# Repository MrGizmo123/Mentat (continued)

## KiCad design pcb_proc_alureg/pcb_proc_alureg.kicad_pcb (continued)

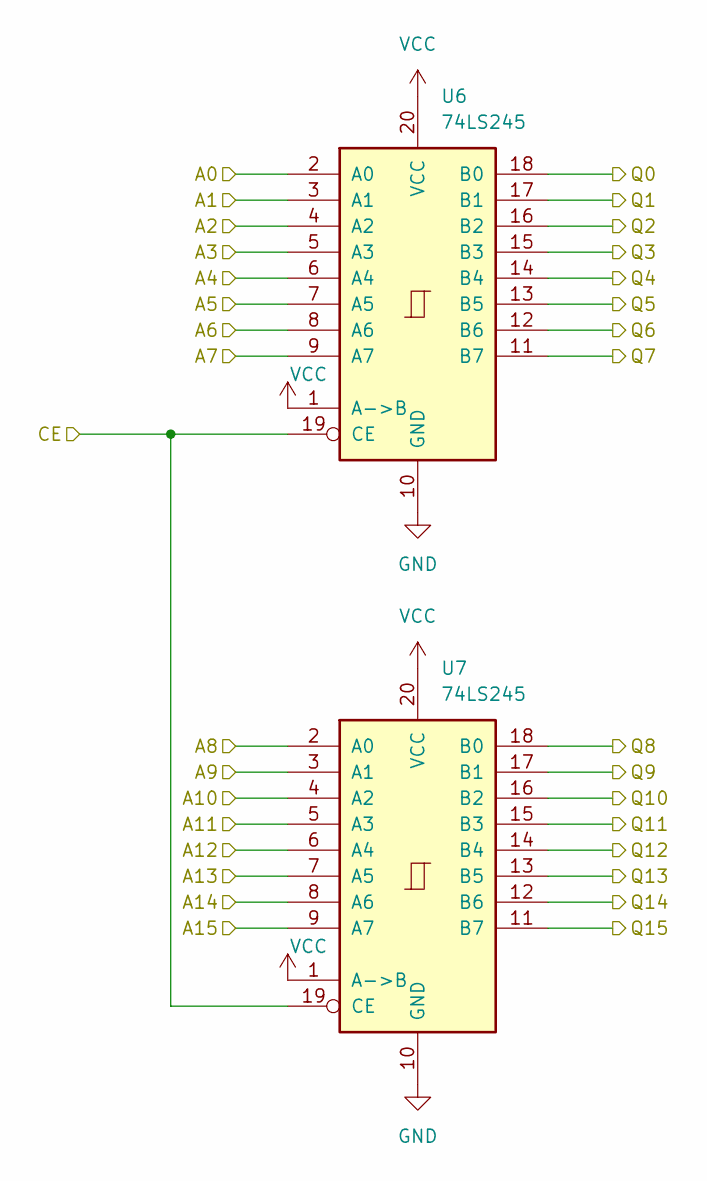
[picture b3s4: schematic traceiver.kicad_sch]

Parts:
U6, U7: 74LS245; DIP-20_W7.62mm_Socket_LongPads

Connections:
/Display/D0: U6.2 (A0); also elsewhere on the board
/Display/D1: U6.3 (A1); also elsewhere on the board
/Display/D2: U6.4 (A2); also elsewhere on the board
/Display/D3: U6.5 (A3); also elsewhere on the board
/Display/D4: U6.6 (A4); also elsewhere on the board
/Display/D5: U6.7 (A5); also elsewhere on the board
/Display/D6: U6.8 (A6); also elsewhere on the board
/Display/D7: U6.9 (A7); also elsewhere on the board
/Display/D8: U7.2 (A0); also elsewhere on the board
/Display/D9: U7.3 (A1); also elsewhere on the board
/Display/D10: U7.4 (A2); also elsewhere on the board
/Display/D11: U7.5 (A3); also elsewhere on the board
/Display/D12: U7.6 (A4); also elsewhere on the board
/Display/D13: U7.7 (A5); also elsewhere on the board
/Display/D14: U7.8 (A6); also elsewhere on the board
/Display/D15: U7.9 (A7); also elsewhere on the board
/Transciever/CE: U6.19 (CE), U7.19 (CE); also elsewhere on the board
/Transciever/Q0: U6.18 (B0); also elsewhere on the board
/Transciever/Q1: U6.17 (B1); also elsewhere on the board
/Transciever/Q2: U6.16 (B2); also elsewhere on the board
/Transciever/Q3: U6.15 (B3); also elsewhere on the board
/Transciever/Q4: U6.14 (B4); also elsewhere on the board
/Transciever/Q5: U6.13 (B5); also elsewhere on the board
/Transciever/Q6: U6.12 (B6); also elsewhere on the board
/Transciever/Q7: U6.11 (B7); also elsewhere on the board
/Transciever/Q8: U7.18 (B0); also elsewhere on the board
/Transciever/Q9: U7.17 (B1); also elsewhere on the board
/Transciever/Q10: U7.16 (B2); also elsewhere on the board
/Transciever/Q11: U7.15 (B3); also elsewhere on the board
/Transciever/Q12: U7.14 (B4); also elsewhere on the board
/Transciever/Q13: U7.13 (B5); also elsewhere on the board
/Transciever/Q14: U7.12 (B6); also elsewhere on the board
/Transciever/Q15: U7.11 (B7); also elsewhere on the board
GND: U6.10 (GND), U7.10 (GND); also elsewhere on the board
VCC: U6.1 (A->B), U6.20 (VCC), U7.1 (A->B), U7.20 (VCC); also elsewhere on the board

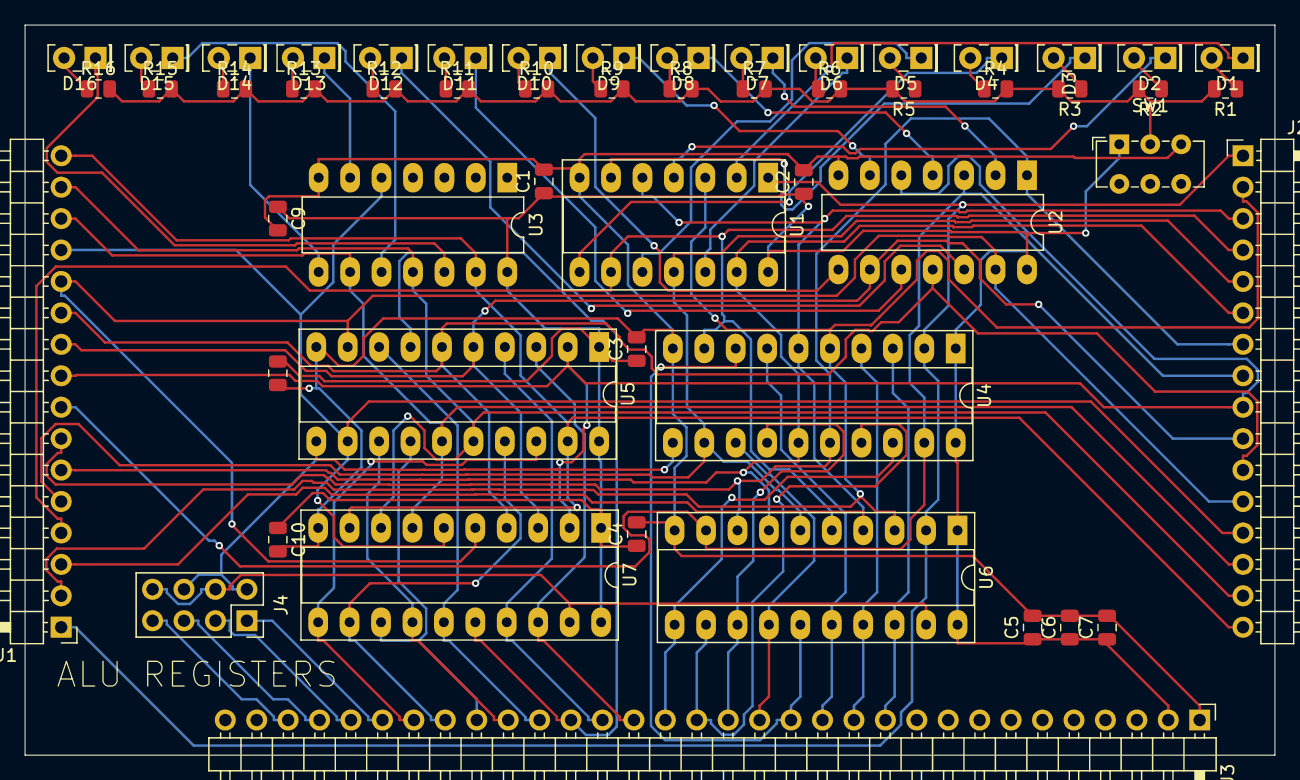
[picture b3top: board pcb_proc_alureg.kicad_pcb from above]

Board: 2 copper layers, 101.0 x 59.0 mm, 54 parts (0 on the bottom side), 73 nets.

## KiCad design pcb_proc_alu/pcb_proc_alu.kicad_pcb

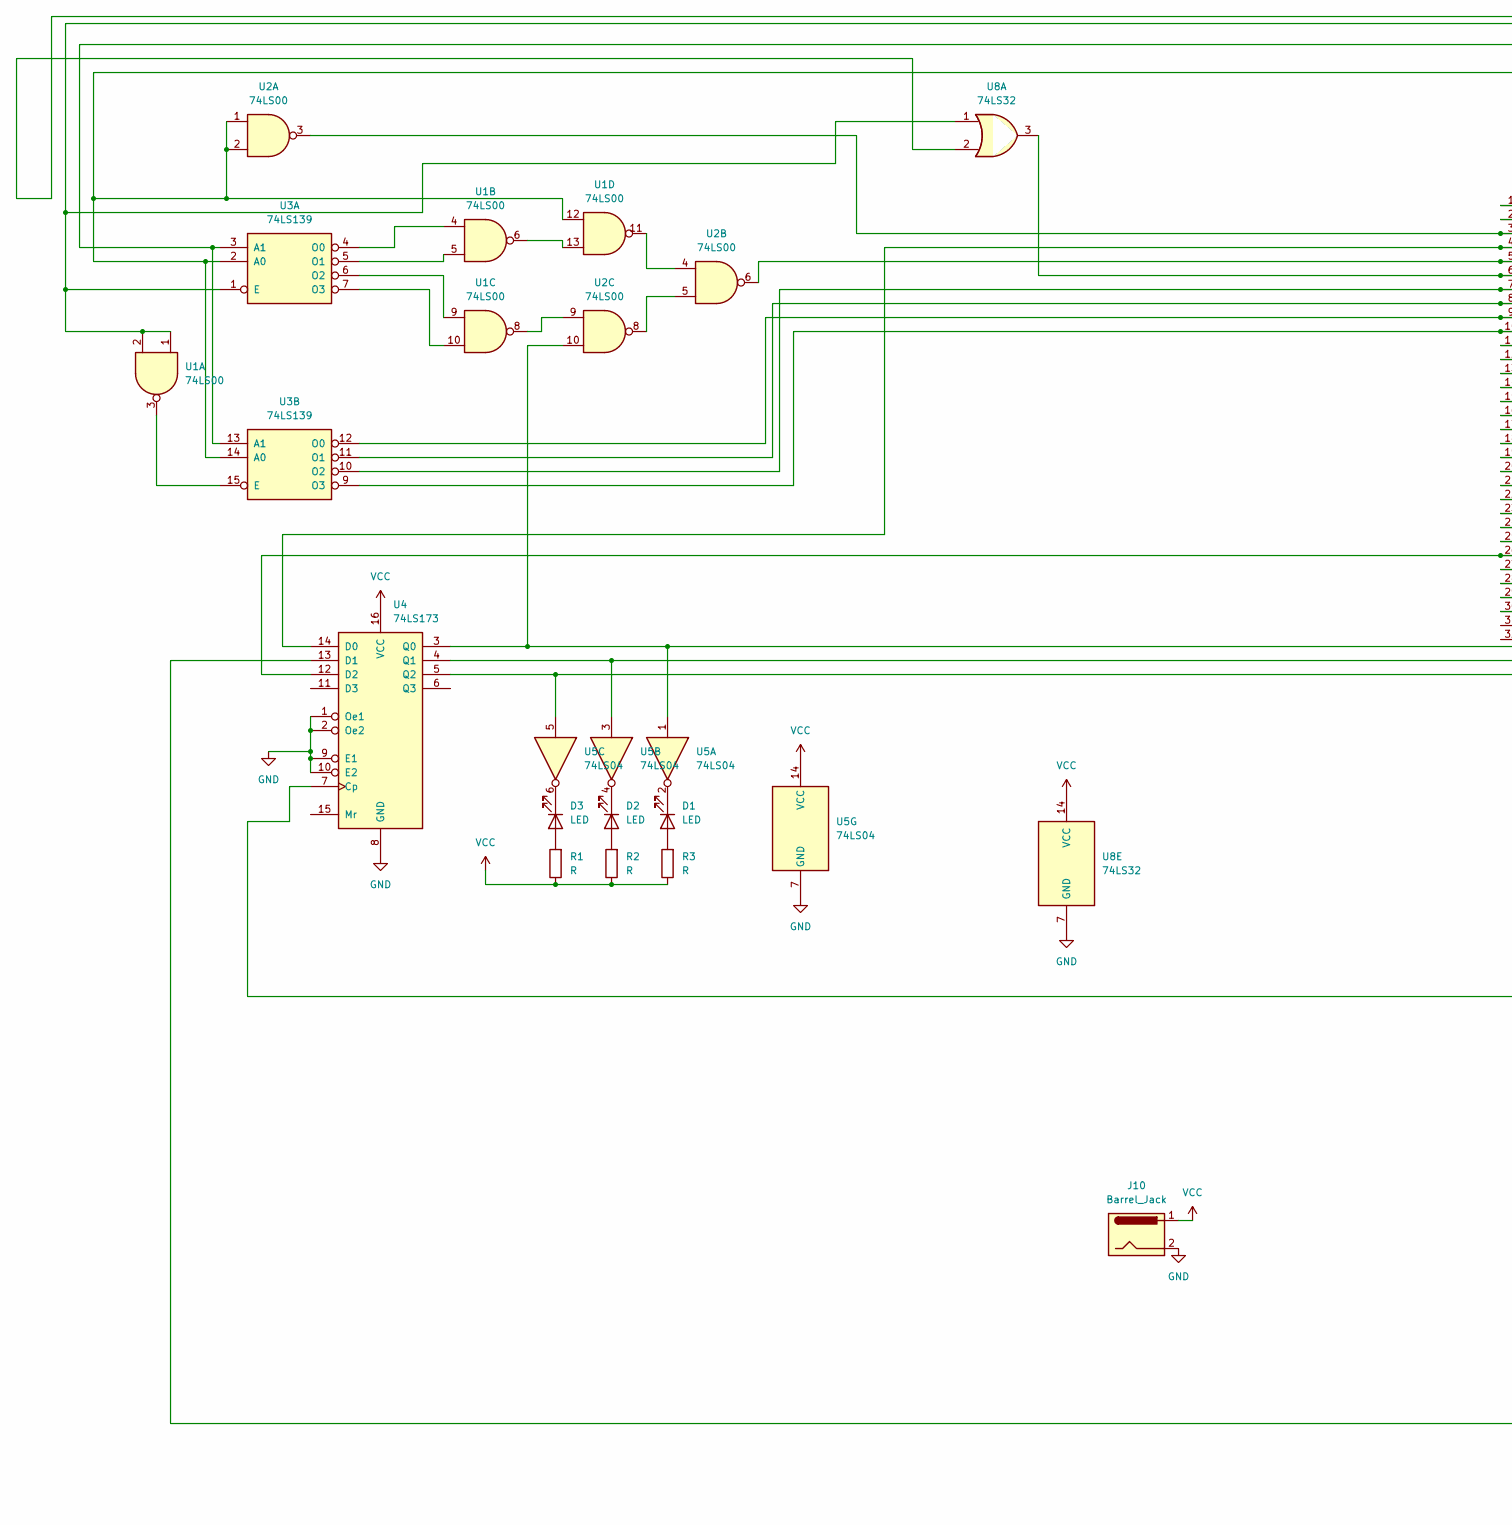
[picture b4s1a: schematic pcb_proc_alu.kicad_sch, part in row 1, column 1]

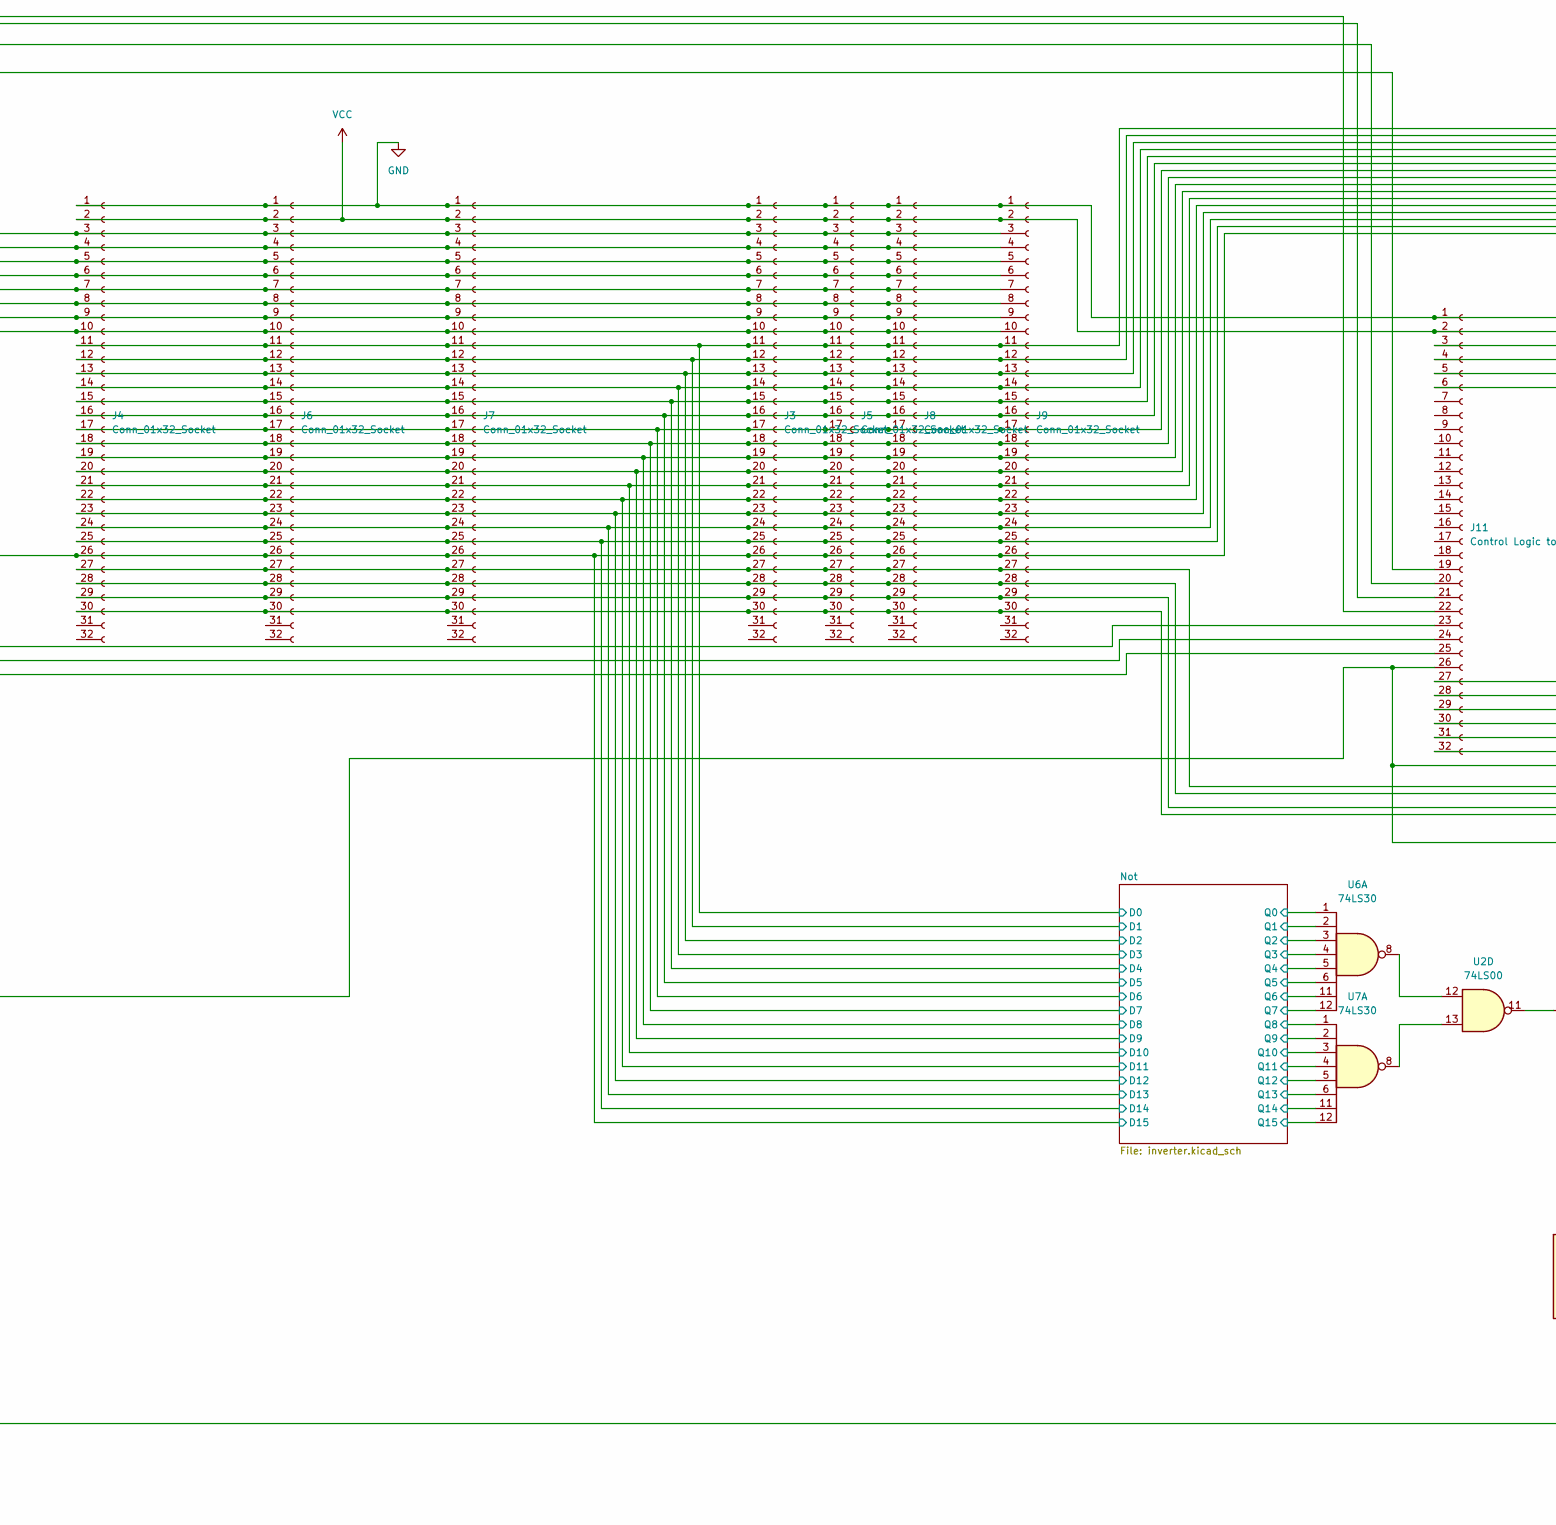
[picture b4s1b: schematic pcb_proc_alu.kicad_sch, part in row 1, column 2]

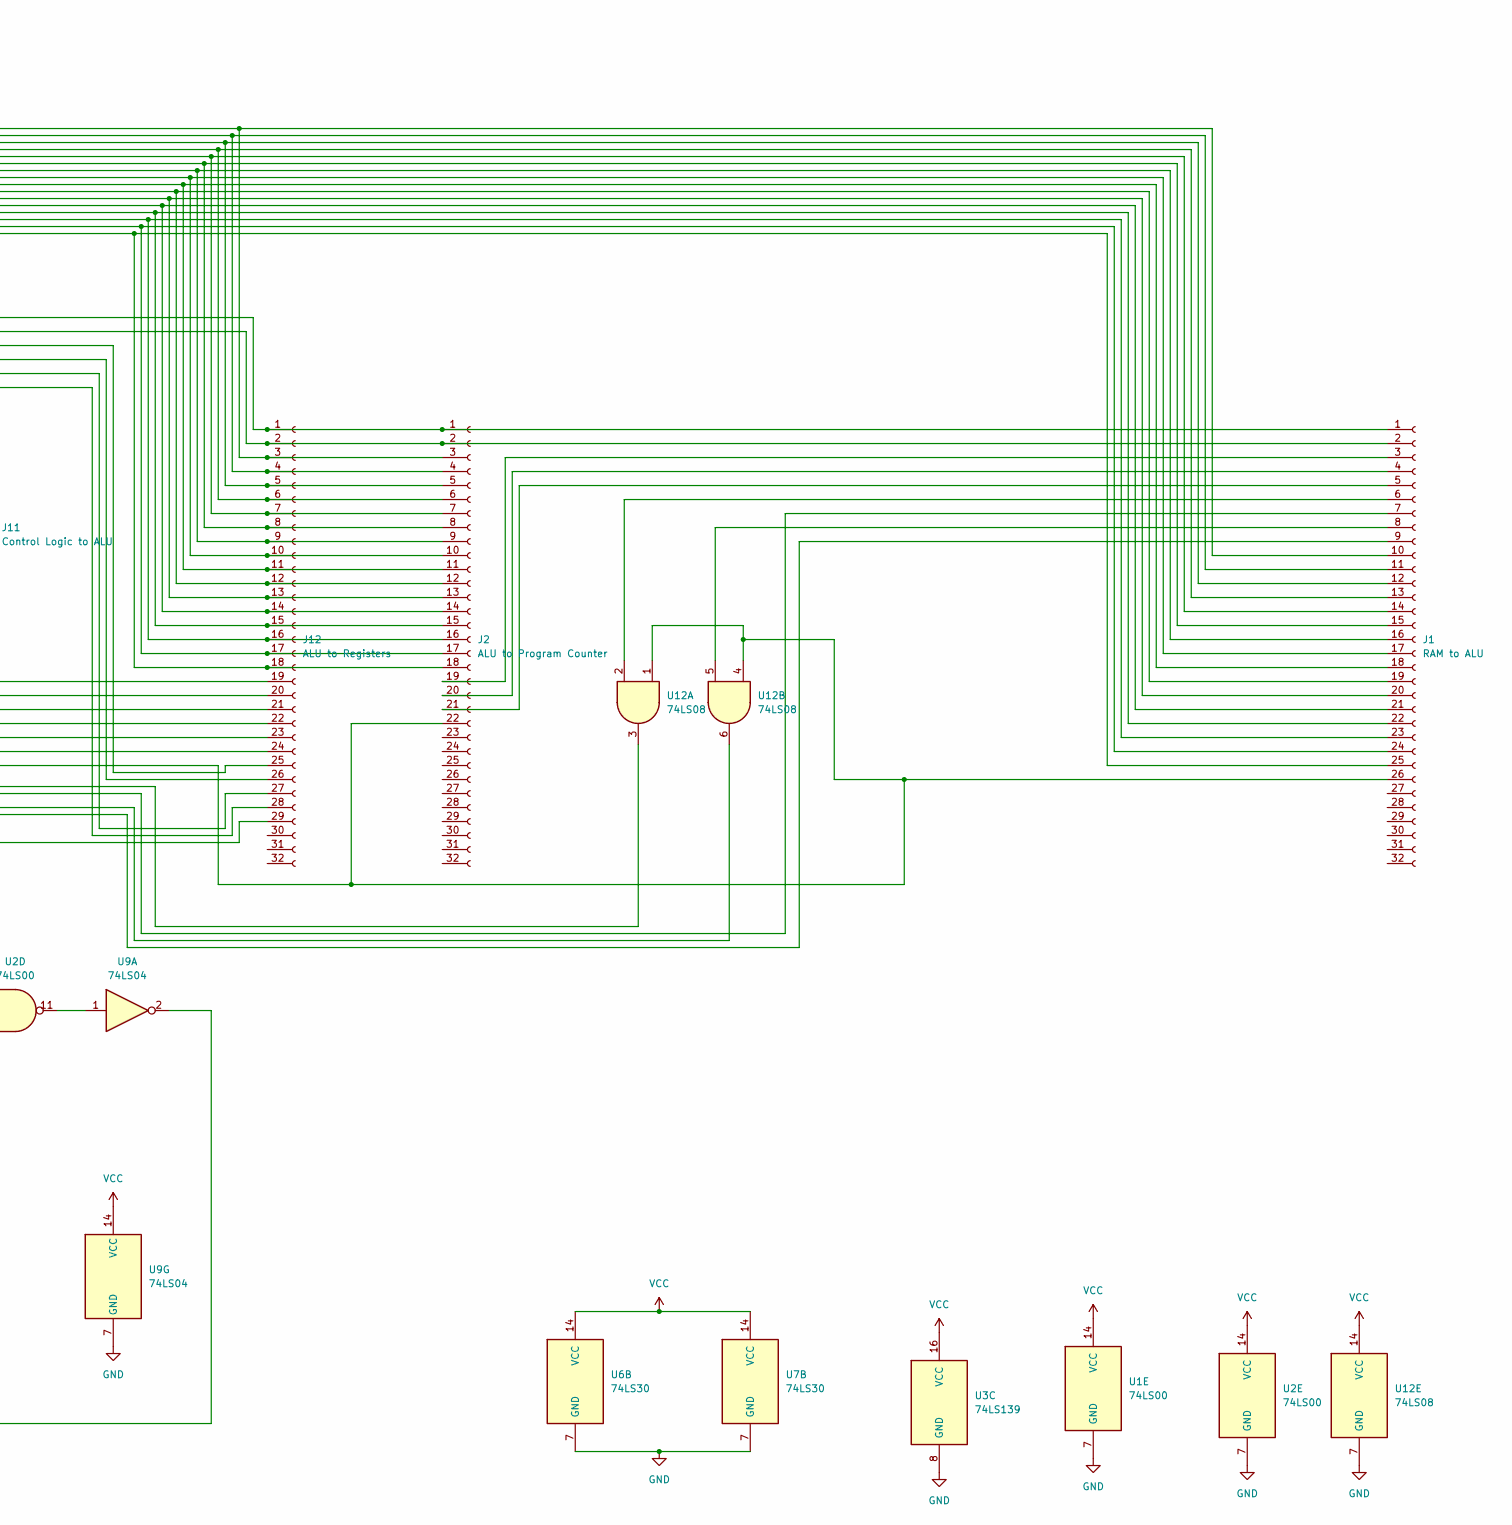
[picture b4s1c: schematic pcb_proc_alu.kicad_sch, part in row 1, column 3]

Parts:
D1, D2, D3: LED; LED_Rectangular_W5.0mm_H2.0mm
J1: RAM to ALU; PinHeader_2x16_P2.54mm_Vertical
J2: ALU to Program Counter; PinHeader_2x16_P2.54mm_Vertical
J3, J4, J5, J6, J7, J8, J9: Conn_01x32_Socket; PinSocket_1x32_P2.54mm_Vertical
J10: Barrel_Jack; BarrelJack_Horizontal
J11: Control Logic to ALU; PinHeader_2x16_P2.54mm_Vertical
J12: ALU to Registers; PinHeader_2x16_P2.54mm_Vertical
R1, R2, R3: R; R_0805_2012Metric
U1, U2: 74LS00; DIP-14_W7.62mm_Socket_LongPads
U3: 74LS139; DIP-16_W7.62mm_Socket_LongPads
U4: 74LS173; DIP-16_W7.62mm_Socket_LongPads
U5, U9: 74LS04; DIP-14_W7.62mm_Socket_LongPads
U6, U7: 74LS30; DIP-14_W7.62mm_Socket_LongPads
U8: 74LS32; DIP-14_W7.62mm_Socket_LongPads
U12: 74LS08; DIP-14_W7.62mm_Socket_LongPads

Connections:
/Not/D0: J1.10, J2.3, J3.11, J4.11, J5.11, J6.11, J7.11, J8.11, J9.11, J12.3; also elsewhere on the board
/Not/D1: J1.11, J2.4, J3.12, J4.12, J5.12, J6.12, J7.12, J8.12, J9.12, J12.4; also elsewhere on the board
/Not/D2: J1.12, J2.5, J3.13, J4.13, J5.13, J6.13, J7.13, J8.13, J9.13, J12.5; also elsewhere on the board
/Not/D3: J1.13, J2.6, J3.14, J4.14, J5.14, J6.14, J7.14, J8.14, J9.14, J12.6; also elsewhere on the board
/Not/D4: J1.14, J2.7, J3.15, J4.15, J5.15, J6.15, J7.15, J8.15, J9.15, J12.7; also elsewhere on the board
/Not/D5: J1.15, J2.8, J3.16, J4.16, J5.16, J6.16, J7.16, J8.16, J9.16, J12.8; also elsewhere on the board
/Not/D6: J1.16, J2.9, J3.17, J4.17, J5.17, J6.17, J7.17, J8.17, J9.17, J12.9; also elsewhere on the board
/Not/D7: J1.17, J2.10, J3.18, J4.18, J5.18, J6.18, J7.18, J8.18, J9.18, J12.10; also elsewhere on the board
/Not/D8: J1.18, J2.11, J3.19, J4.19, J5.19, J6.19, J7.19, J8.19, J9.19, J12.11; also elsewhere on the board
/Not/D9: J1.19, J2.12, J3.20, J4.20, J5.20, J6.20, J7.20, J8.20, J9.20, J12.12; also elsewhere on the board
/Not/D10: J1.20, J2.13, J3.21, J4.21, J5.21, J6.21, J7.21, J8.21, J9.21, J12.13; also elsewhere on the board
/Not/D11: J1.21, J2.14, J3.22, J4.22, J5.22, J6.22, J7.22, J8.22, J9.22, J12.14; also elsewhere on the board
/Not/D12: J1.22, J2.15, J3.23, J4.23, J5.23, J6.23, J7.23, J8.23, J9.23, J12.15; also elsewhere on the board
/Not/D13: J1.23, J2.16, J3.24, J4.24, J5.24, J6.24, J7.24, J8.24, J9.24, J12.16; also elsewhere on the board
/Not/D14: J1.24, J2.17, J3.25, J4.25, J5.25, J6.25, J7.25, J8.25, J9.25, J12.17; also elsewhere on the board
/Not/D15: J1.25, J2.18, J3.26, J4.26, J5.26, J6.26, J7.26, J8.26, J9.26, J12.18, U4.12 (D2); also elsewhere on the board
/Not/Q0: U6.1; also elsewhere on the board
/Not/Q1: U6.2; also elsewhere on the board
/Not/Q2: U6.3; also elsewhere on the board
/Not/Q3: U6.4; also elsewhere on the board
/Not/Q4: U6.5; also elsewhere on the board
/Not/Q5: U6.6; also elsewhere on the board
/Not/Q6: U6.11; also elsewhere on the board
/Not/Q7: U6.12; also elsewhere on the board
/Not/Q8: U7.1; also elsewhere on the board
/Not/Q9: U7.2; also elsewhere on the board
/Not/Q10: U7.3; also elsewhere on the board
/Not/Q11: U7.4; also elsewhere on the board
/Not/Q12: U7.5; also elsewhere on the board
/Not/Q13: U7.6; also elsewhere on the board
/Not/Q14: U7.11; also elsewhere on the board
/Not/Q15: U7.12; also elsewhere on the board
GND: J1.1, J2.1, J3.1, J4.1, J5.1, J6.1, J7.1, J8.1, J9.1, J10.2, J11.1, J12.1, U1.7 (GND), U2.7 (GND), U3.8 (GND), U4.1 (Oe1), U4.2 (Oe2), U4.8 (GND), U4.9 (E1), U4.10 (E2), U5.7 (GND), U6.7 (GND), U7.7 (GND), U8.7 (GND), U9.7 (GND), U12.7 (GND); also elsewhere on the board
unnamed: D1.2 (A), R3.2
unnamed: D1.1 (K), U5.2
unnamed: D2.2 (A), R2.2
unnamed: D2.1 (K), U5.4
unnamed: D3.2 (A), R1.2
unnamed: D3.1 (K), U5.6
unnamed: J1.3, J2.19
unnamed: J1.4, J2.20
unnamed: J1.5, J2.21
unnamed: J1.6, U12.2
unnamed: J1.7, J3.28, J4.28, J5.28, J6.28, J7.28, J8.28, J9.28
unnamed: J1.8, U12.5
unnamed: J1.9, J3.30, J4.30, J5.30, J6.30, J7.30, J8.30, J9.30
unnamed: J1.26, J2.22, J11.26, J12.29, U4.7 (Cp), U12.1, U12.4
unnamed: J3.3, J4.3, J5.3, J6.3, J7.3, J8.3, J9.3, U2.3
unnamed: J3.4, J4.4, J5.4, J6.4, J7.4, J8.4, J9.4, U4.14 (D0)
unnamed: J3.5, J4.5, J5.5, J6.5, J7.5, J8.5, J9.5, U2.6
unnamed: J3.6, J4.6, J5.6, J6.6, J7.6, J8.6, J9.6, U8.3
unnamed: J3.7, J4.7, J5.7, J6.7, J7.7, J8.7, J9.7, U3.10 (O2)
unnamed: J3.8, J4.8, J5.8, J6.8, J7.8, J8.8, J9.8, U3.11 (O1)
unnamed: J3.9, J4.9, J5.9, J6.9, J7.9, J8.9, J9.9, U3.12 (O0)
unnamed: J3.10, J4.10, J5.10, J6.10, J7.10, J8.10, J9.10, U3.9 (O3)
unnamed: J3.27, J4.27, J5.27, J6.27, J7.27, J8.27, J9.27, U12.3
unnamed: J3.29, J4.29, J5.29, J6.29, J7.29, J8.29, J9.29, U12.6
unnamed: J11.3, J12.25
unnamed: J11.4, J12.26
unnamed: J11.5, J12.27
unnamed: J11.6, J12.28
unnamed: J11.19, U1.12, U2.1, U2.2, U3.2 (A0), U3.14 (A0)
unnamed: J11.20, U3.3 (A1), U3.13 (A1)
unnamed: J11.21, U1.1, U1.2, U3.1 (E), U8.1
unnamed: J11.22, U8.2
unnamed: J11.23, U2.10, U4.3 (Q0), U5.1
unnamed: J11.24, U4.4 (Q1), U5.3
unnamed: J11.25, U4.5 (Q2), U5.5
unnamed: J11.27, J12.19
unnamed: J11.28, J12.20
unnamed: J11.29, J12.21
unnamed: J11.30, J12.22
unnamed: J11.31, J12.23
unnamed: J11.32, J12.24
unnamed: U1.8, U2.9
unnamed: U1.11, U2.4
unnamed: U1.6, U1.13
unnamed: U2.5, U2.8
unnamed: U2.11, U9.1
unnamed: U2.12, U6.8
unnamed: U2.13, U7.8
unnamed: U1.4, U3.4 (O0)
unnamed: U1.5, U3.5 (O1)
unnamed: U1.9, U3.6 (O2)
unnamed: U1.10, U3.7 (O3)
unnamed: U1.3, U3.15 (E)
unnamed: U4.13 (D1), U9.2
VCC: J1.2, J2.2, J3.2, J4.2, J5.2, J6.2, J7.2, J8.2, J9.2, J10.1, J11.2, J12.2, R1.1, R2.1, R3.1, U1.14 (VCC), U2.14 (VCC), U3.16 (VCC), U4.16 (VCC), U5.14 (VCC), U6.14 (VCC), U7.14 (VCC), U8.14 (VCC), U9.14 (VCC), U12.14 (VCC); also elsewhere on the board

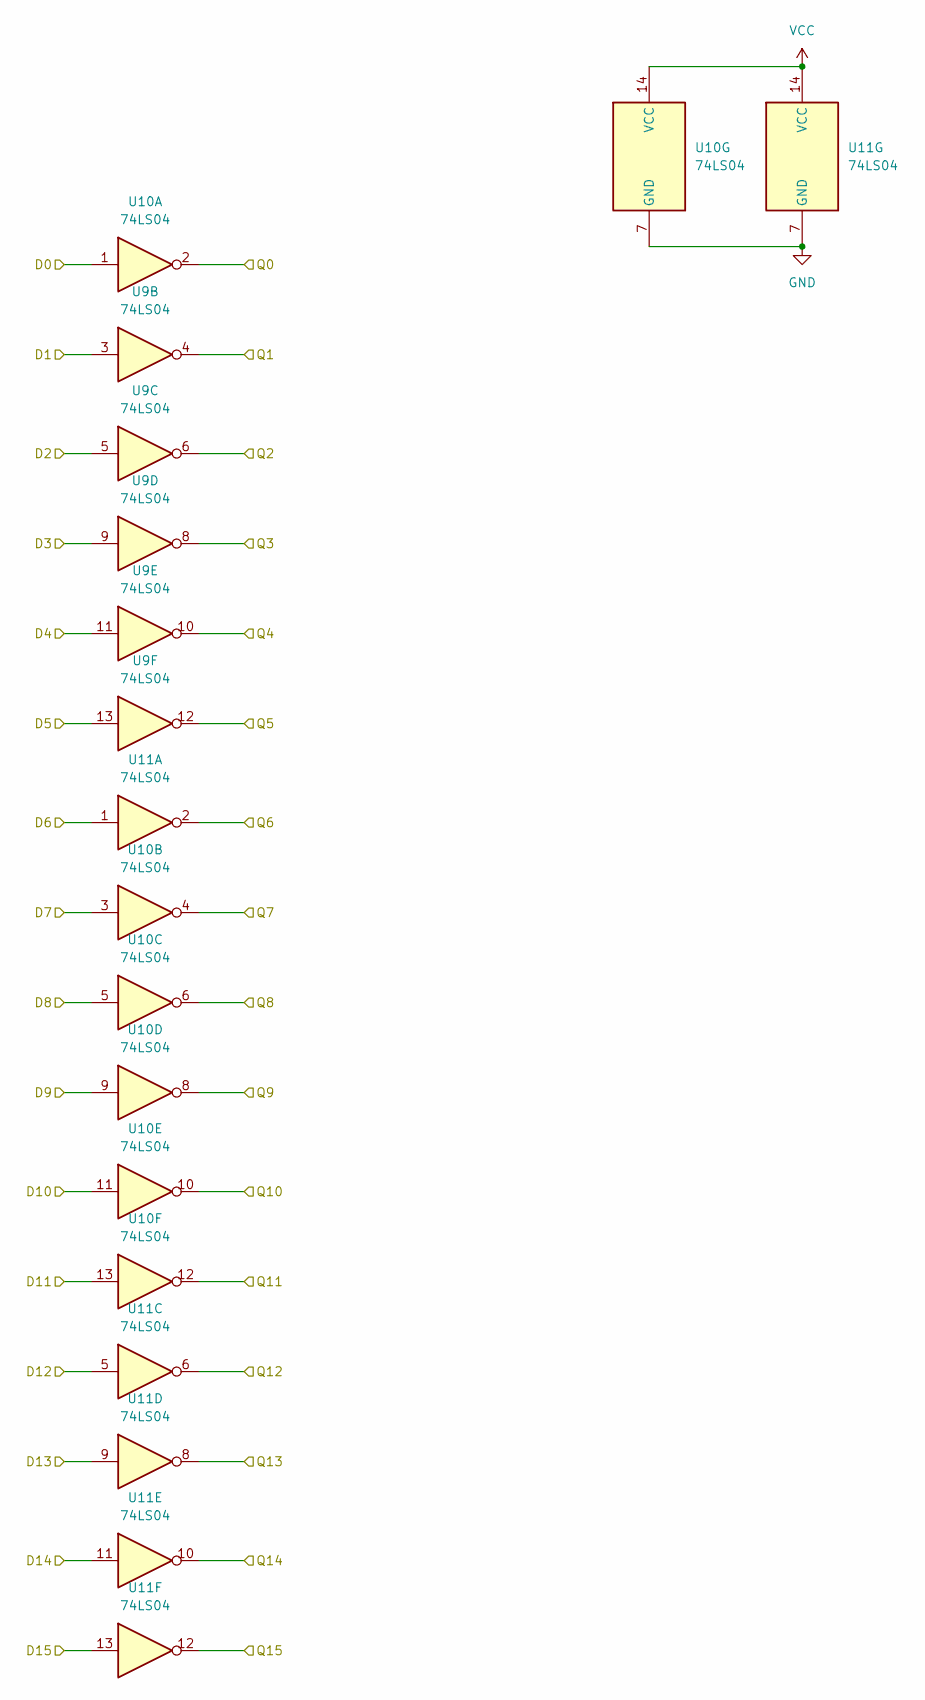
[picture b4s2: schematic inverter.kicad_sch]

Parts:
U9, U10, U11: 74LS04; DIP-14_W7.62mm_Socket_LongPads

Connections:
/Not/D0: U10.1; also elsewhere on the board
/Not/D1: U9.3; also elsewhere on the board
/Not/D2: U9.5; also elsewhere on the board
/Not/D3: U9.9; also elsewhere on the board
/Not/D4: U9.11; also elsewhere on the board
/Not/D5: U9.13; also elsewhere on the board
/Not/D6: U11.1; also elsewhere on the board
/Not/D7: U10.3; also elsewhere on the board
/Not/D8: U10.5; also elsewhere on the board
/Not/D9: U10.9; also elsewhere on the board
/Not/D10: U10.11; also elsewhere on the board
/Not/D11: U10.13; also elsewhere on the board
/Not/D12: U11.5; also elsewhere on the board
/Not/D13: U11.9; also elsewhere on the board
/Not/D14: U11.11; also elsewhere on the board
/Not/D15: U11.13; also elsewhere on the board
/Not/Q0: U10.2; also elsewhere on the board
/Not/Q1: U9.4; also elsewhere on the board
/Not/Q2: U9.6; also elsewhere on the board
/Not/Q3: U9.8; also elsewhere on the board
/Not/Q4: U9.10; also elsewhere on the board
/Not/Q5: U9.12; also elsewhere on the board
/Not/Q6: U11.2; also elsewhere on the board
/Not/Q7: U10.4; also elsewhere on the board
/Not/Q8: U10.6; also elsewhere on the board
/Not/Q9: U10.8; also elsewhere on the board
/Not/Q10: U10.10; also elsewhere on the board
/Not/Q11: U10.12; also elsewhere on the board
/Not/Q12: U11.6; also elsewhere on the board
/Not/Q13: U11.8; also elsewhere on the board
/Not/Q14: U11.10; also elsewhere on the board
/Not/Q15: U11.12; also elsewhere on the board
GND: U10.7 (GND), U11.7 (GND); also elsewhere on the board
VCC: U10.14 (VCC), U11.14 (VCC); also elsewhere on the board

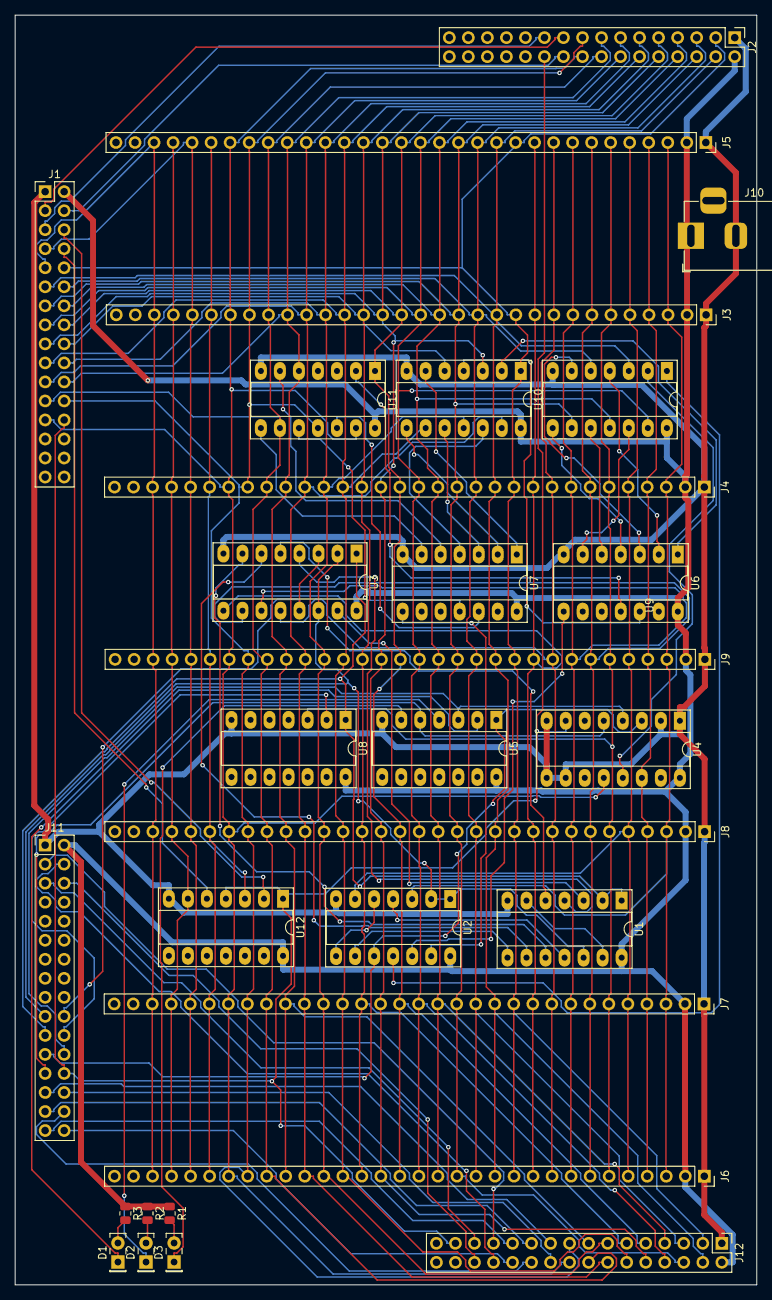
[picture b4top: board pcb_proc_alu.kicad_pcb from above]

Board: 2 copper layers, 99.0 x 169.5 mm, 30 parts (0 on the bottom side), 88 nets.
